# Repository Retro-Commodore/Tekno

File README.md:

# Tekno
Tekno kit from Catus - Electronics controller using your Amiga

Yet another reverse product from e5frog.

https://bigbookofamigahardware.com/bboah/product.aspx?id=722

#

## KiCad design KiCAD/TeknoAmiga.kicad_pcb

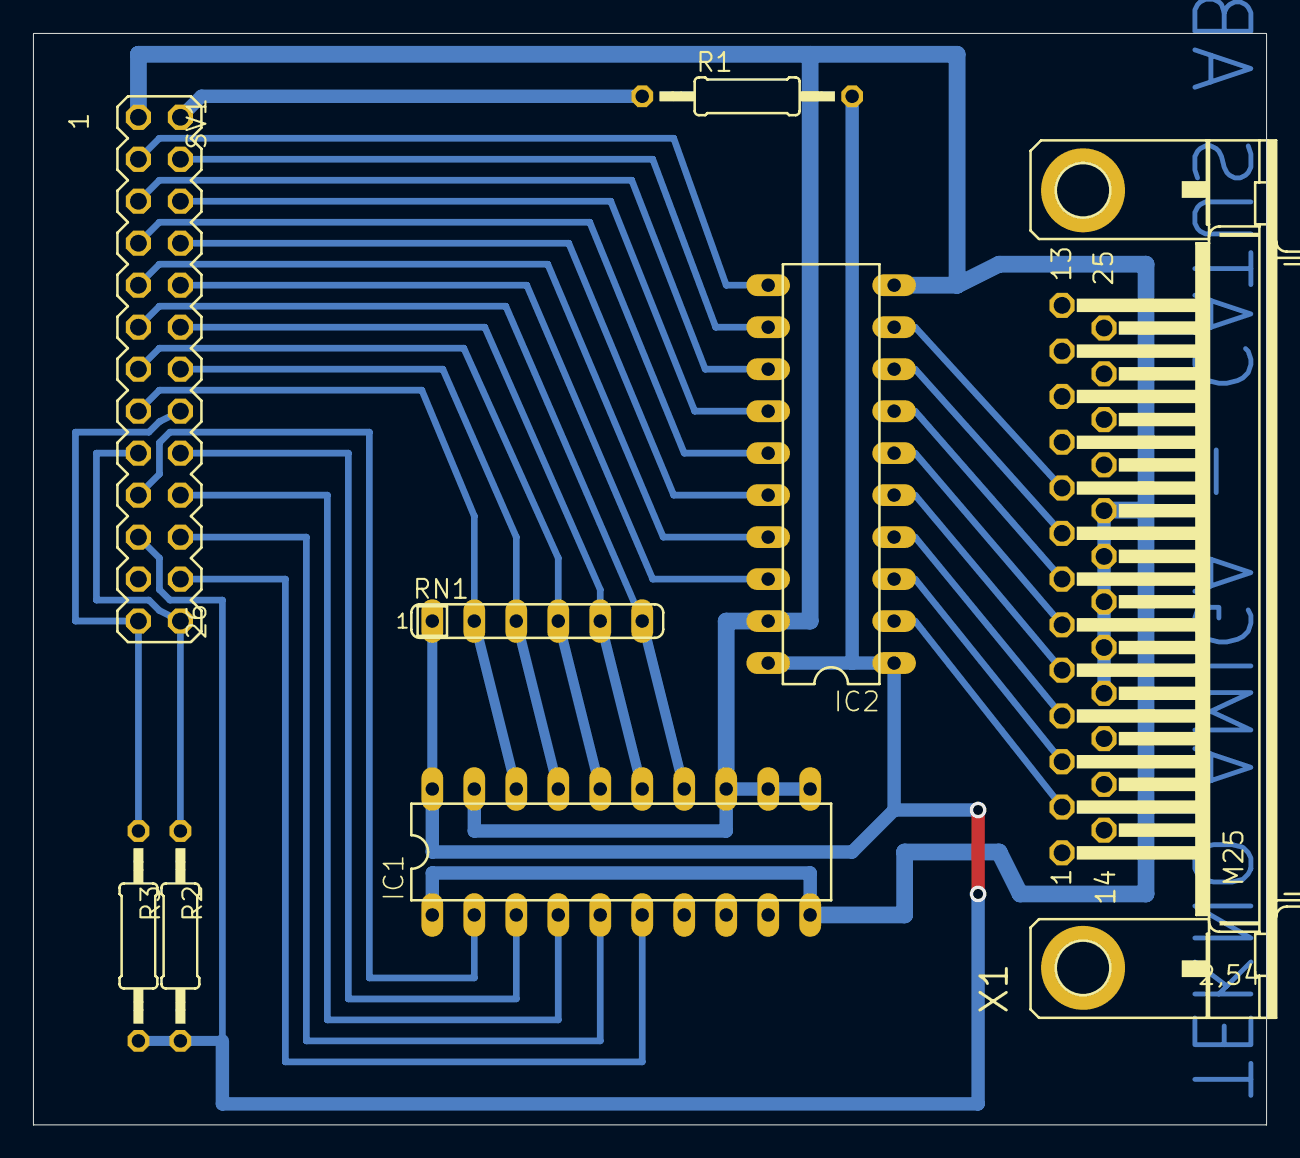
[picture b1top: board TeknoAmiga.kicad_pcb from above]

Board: 2 copper layers, 74.6 x 66.0 mm, 8 parts (0 on the bottom side), 31 nets.

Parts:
IC1, IC2: 74LS245N; DIL20
R1: 47; 0207_12
R2, R3: 680k; 0207_12
RN1: 22k; SIL6
SV1: MA13-2
X1: M25HP

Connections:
GND: IC1.1, IC1.10, IC1.11, IC1.12, IC1.13, IC1.19, IC2.10, IC2.19, SV1.1, X1.17, X1.18, X1.19, X1.20, X1.21, X1.22, X1.23, X1.24, X1.25
unnamed: IC2.2, X1.2
unnamed: IC2.3, X1.3
unnamed: IC2.4, X1.4
unnamed: IC2.5, X1.5
unnamed: IC2.6, X1.6
unnamed: IC2.7, X1.7
unnamed: IC2.8, X1.8
unnamed: IC2.9, X1.9
unnamed: IC1.14, RN1.6, SV1.11
unnamed: IC1.15, RN1.5, SV1.12
unnamed: IC1.16, RN1.4, SV1.13
unnamed: IC1.17, RN1.3, SV1.14
unnamed: IC1.18, RN1.2, SV1.15
unnamed: R2.1, SV1.17, SV1.26
unnamed: R3.1, SV1.16, SV1.25
unnamed: IC1.6, SV1.24
unnamed: IC1.5, SV1.22
unnamed: IC1.4, SV1.20
unnamed: IC1.3, SV1.18
unnamed: IC1.2, SV1.19
unnamed: R1.1, SV1.2
unnamed: IC2.11, SV1.3
unnamed: IC2.12, SV1.4
unnamed: IC2.13, SV1.5
unnamed: IC2.14, SV1.6
unnamed: IC2.15, SV1.7
unnamed: IC2.16, SV1.8
unnamed: IC2.17, SV1.9
unnamed: IC2.18, SV1.10
VCC: IC1.20, IC2.1, IC2.20, R1.2, R2.2, R3.2, RN1.1, SV1.21

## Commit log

2023-05-29 added kicad version + 3d image
2023-05-29 remove backups
